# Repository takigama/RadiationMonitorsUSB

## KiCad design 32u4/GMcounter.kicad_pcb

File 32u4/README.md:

Geiger Counter
==============

Based on MightyOhms GM Device, this is an SMD version of that device
with a 32u4 atmel chip onboard.

Tag firtprint has now been sent to the printer and looks like this:

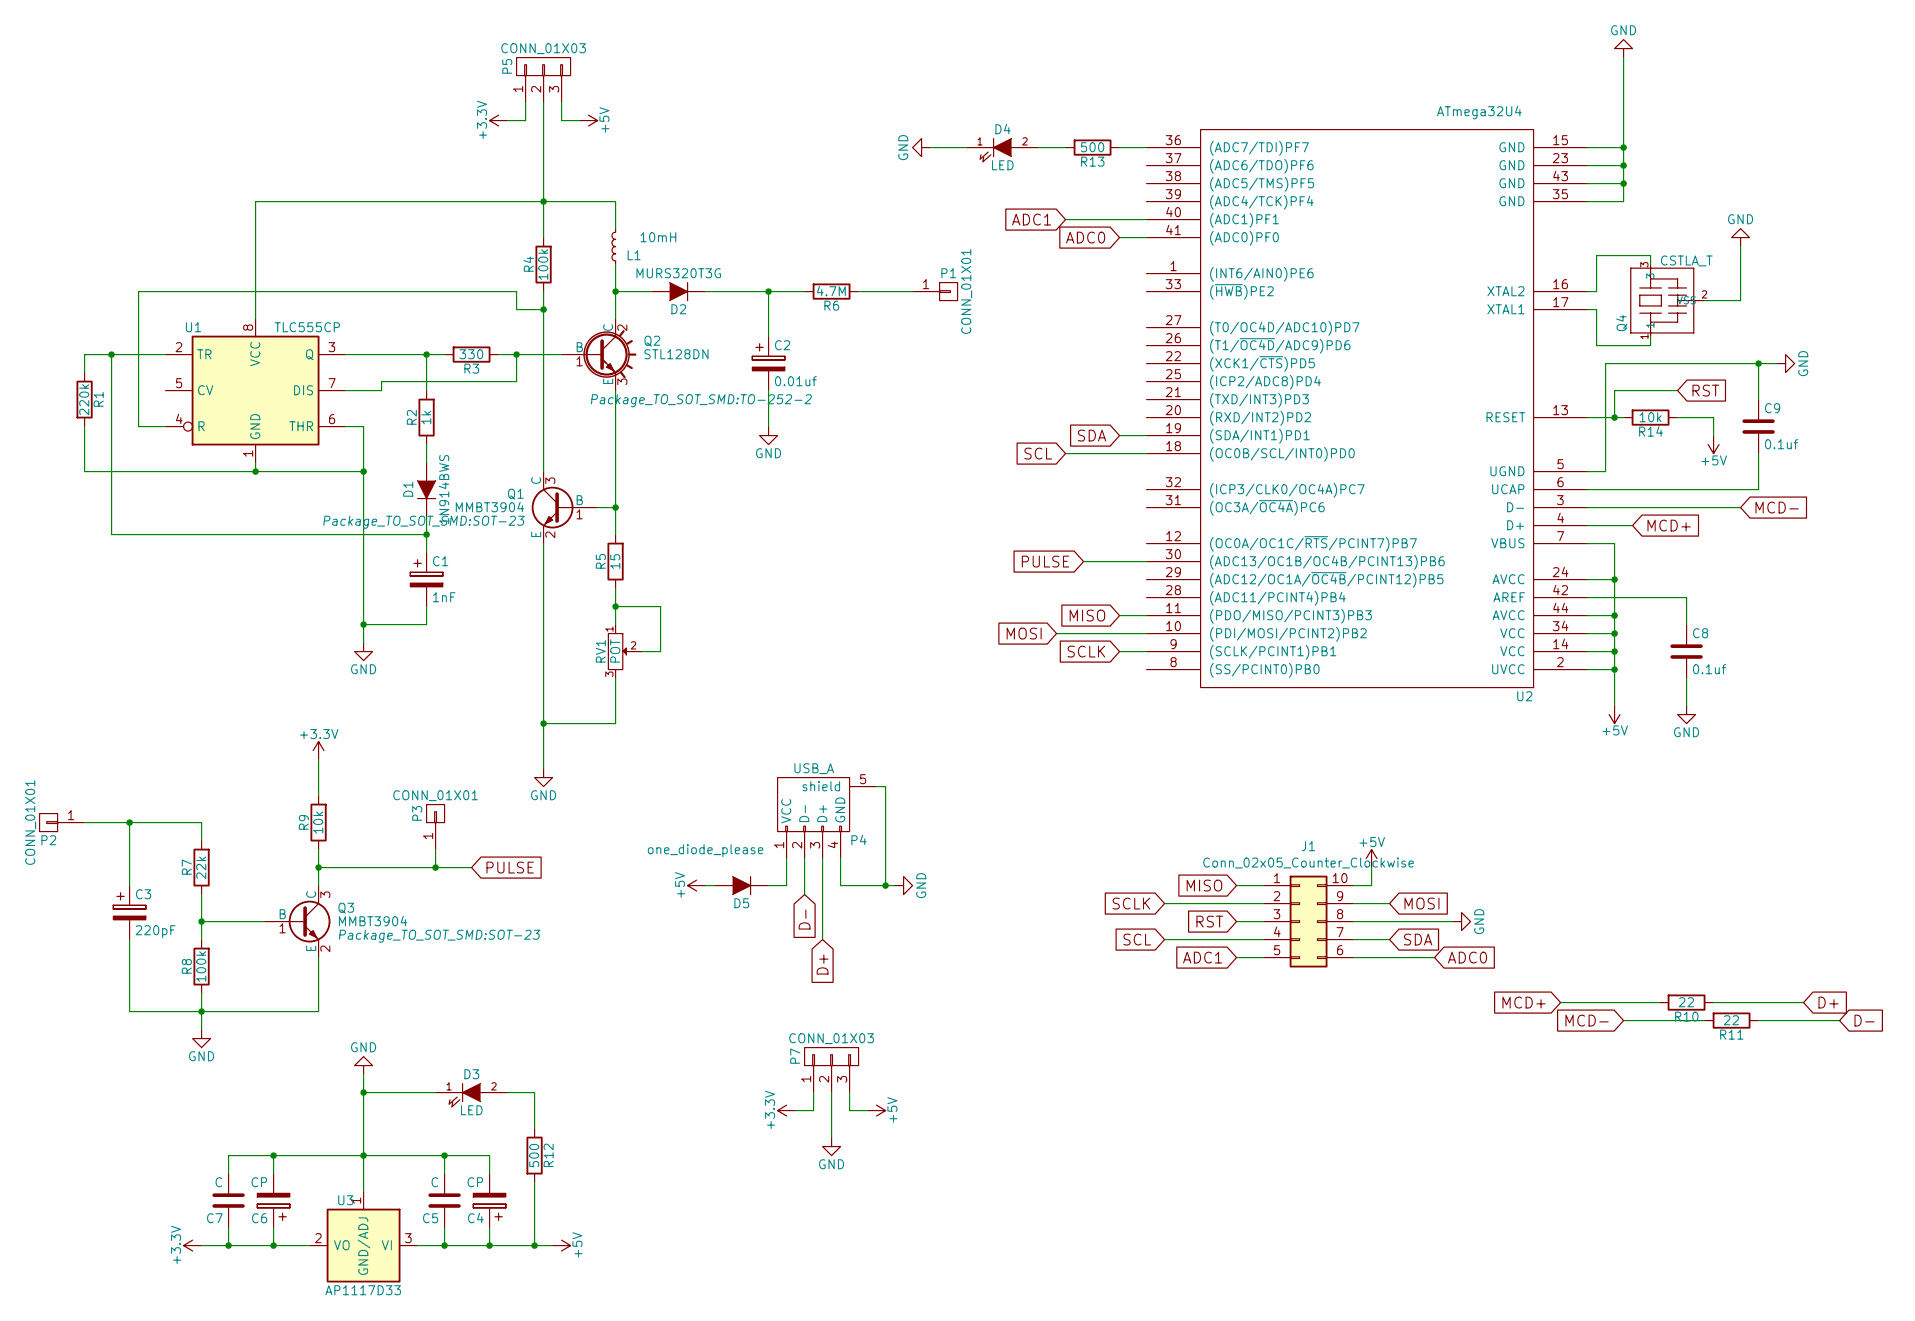
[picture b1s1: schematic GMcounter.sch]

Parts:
C1: 1nF; CP_EIA-3216-12_Kemet-S
C2: 0.01uf; CP_EIA-3216-12_Kemet-S
C3: 220pF; CP_EIA-3216-12_Kemet-S
C4, C6: CP; CP_EIA-3216-12_Kemet-S
C5, C7: C; C_1206_3216Metric
C8, C9: 0.1uf; C_1206_3216Metric
D1: 1N914BWS; D_SOD-323
D2: MURS320T3G; D_SMC
D3, D4: LED; D_0805_2012Metric
D5: one_diode_please; D_SMA
J1: Conn_02x05_Counter_Clockwise; PinHeader_2x05_P2.54mm_Vertical
L1: 10mH; SRR1208
P1, P2, P3: CONN_01X01; PinHeader_1x01_P2.54mm_Vertical
P4: USB_A; USB_Micro-B-OshPark
P5, P7: CONN_01X03; PinHeader_1x03_P2.54mm_Vertical
Q1, Q3: MMBT3904; SOT-23
Q2: STL128DN; TO-252-2
Q4: CSTLA_T; Murata-16mhz-Resonator
R1: 220k; R_1206_3216Metric
R2: 1k; R_1206_3216Metric
R3: 330; R_1206_3216Metric
R4, R8: 100k; R_1206_3216Metric
R5: 15; R_1206_3216Metric
R6: 4.7M; R_1206_3216Metric
R7: 22k; R_1206_3216Metric
R9, R14: 10k; R_1206_3216Metric
R10, R11: 22; R_1206_3216Metric
R12, R13: 500; R_1206_3216Metric
RV1: POT; Potentiometer_Bourns_3296W_Vertical
U1: TLC555CP; SOIC-8_3.9x4.9mm_P1.27mm
U2: ATmega32U4; TQFP-44_10x10mm_P0.8mm
U3: AP1117D33; SOT-223

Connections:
+3V3: C6.1, C7.1, P5.1, P7.1, R9.2, U3.2 (VO)
+5V: C4.1, C5.1, D5.2 (A), J1.10, P5.3, P7.3, R12.2, R14.1, U2.2 (UVCC), U2.7 (VBUS), U2.14 (VCC), U2.24 (AVCC), U2.34 (VCC), U2.44 (AVCC), U3.3 (VI)
ADC0: J1.6, U2.41 ((ADC0)PF0)
ADC1: J1.5, U2.40 ((ADC1)PF1)
D+: P4.3 (D+), R10.1
D-: P4.2 (D-), R11.1
GND: C1.2, C2.2, C3.2, C4.2, C5.2, C6.2, C7.2, C8.2, C9.1, D3.1 (K), D4.1 (K), J1.8, P4.4 (GND), P4.5 (shield), P7.2, Q1.2 (E), Q3.2 (E), Q4.2 (VSS), R1.2, R8.1, RV1.3, U1.1 (GND), U1.6 (THR), U2.5 (UGND), U2.15 (GND), U2.23 (GND), U2.35 (GND), U2.43 (GND), U3.1 (GND/ADJ)
MCD+: R10.2, U2.4 (D+)
MCD-: R11.2, U2.3 (D-)
MISO: J1.1, U2.11 ((PDO/MISO/PCINT3)PB3)
MOSI: J1.9, U2.10 ((PDI/MOSI/PCINT2)PB2)
unnamed: C1.1, D1.1 (K), R1.1, U1.2 (TR)
unnamed: C2.1, D2.1 (K), R6.2
unnamed: C3.1, P2.1, R7.2
unnamed: C8.1, U2.42 (AREF)
unnamed: C9.2, U2.6 (UCAP)
unnamed: D1.2 (A), R2.1
unnamed: D2.2 (A), L1.1, Q2.2 (C)
unnamed: D3.2 (A), R12.1
unnamed: D4.2 (A), R13.2
unnamed: D5.1 (K), P4.1 (VCC)
unnamed: L1.2, P5.2, R4.2, U1.8 (VCC)
unnamed: P1.1, R6.1
unnamed: Q1.1 (B), Q2.3 (E), R5.2
unnamed: Q1.3 (C), R4.1, U1.4 (R)
unnamed: Q2.1 (B), R3.1, U1.7 (DIS)
unnamed: Q3.1 (B), R7.1, R8.2
unnamed: Q4.1, U2.17 (XTAL1)
unnamed: Q4.3, U2.16 (XTAL2)
unnamed: R2.2, R3.2, U1.3 (Q)
unnamed: R5.1, RV1.1, RV1.2
unnamed: R13.1, U2.36 ((ADC7/TDI)PF7)
PULSE: P3.1, Q3.3 (C), R9.1, U2.30 ((ADC13/OC1B/OC4B/PCINT13)PB6)
RST: J1.3, R14.2, U2.13 (RESET)
SCL: J1.4, U2.18 ((OC0B/SCL/INT0)PD0)
SCLK: J1.2, U2.9 ((SCLK/PCINT1)PB1)
SDA: J1.7, U2.19 ((SDA/INT1)PD1)

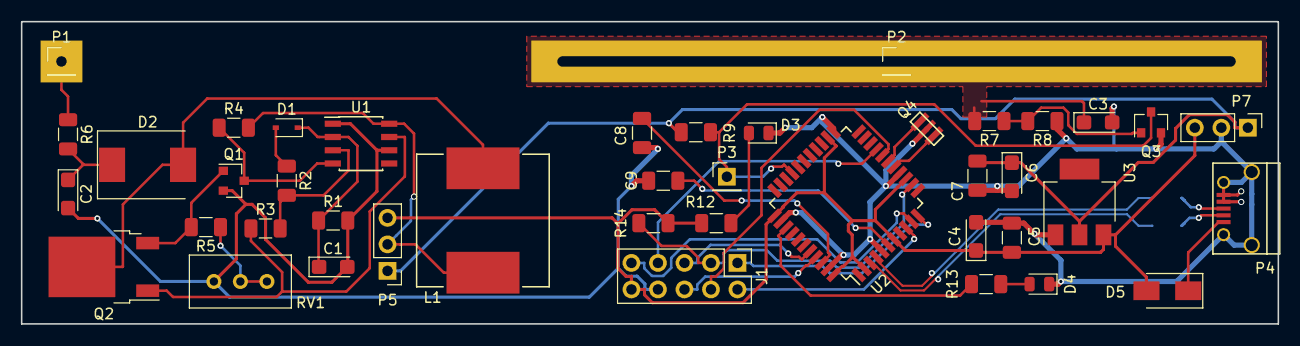
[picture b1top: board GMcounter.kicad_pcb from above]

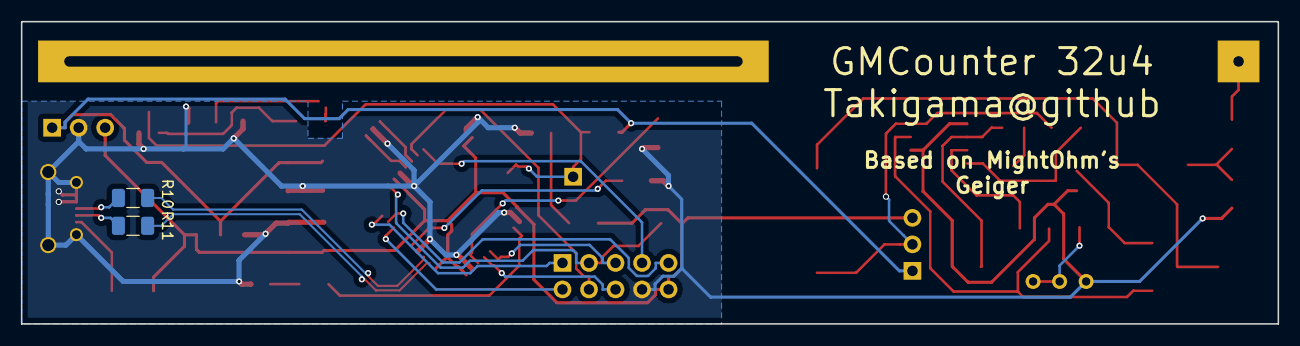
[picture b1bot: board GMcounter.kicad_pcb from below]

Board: 2 copper layers, 120.4 x 29.0 mm, 44 parts (2 on the bottom side), 37 nets.

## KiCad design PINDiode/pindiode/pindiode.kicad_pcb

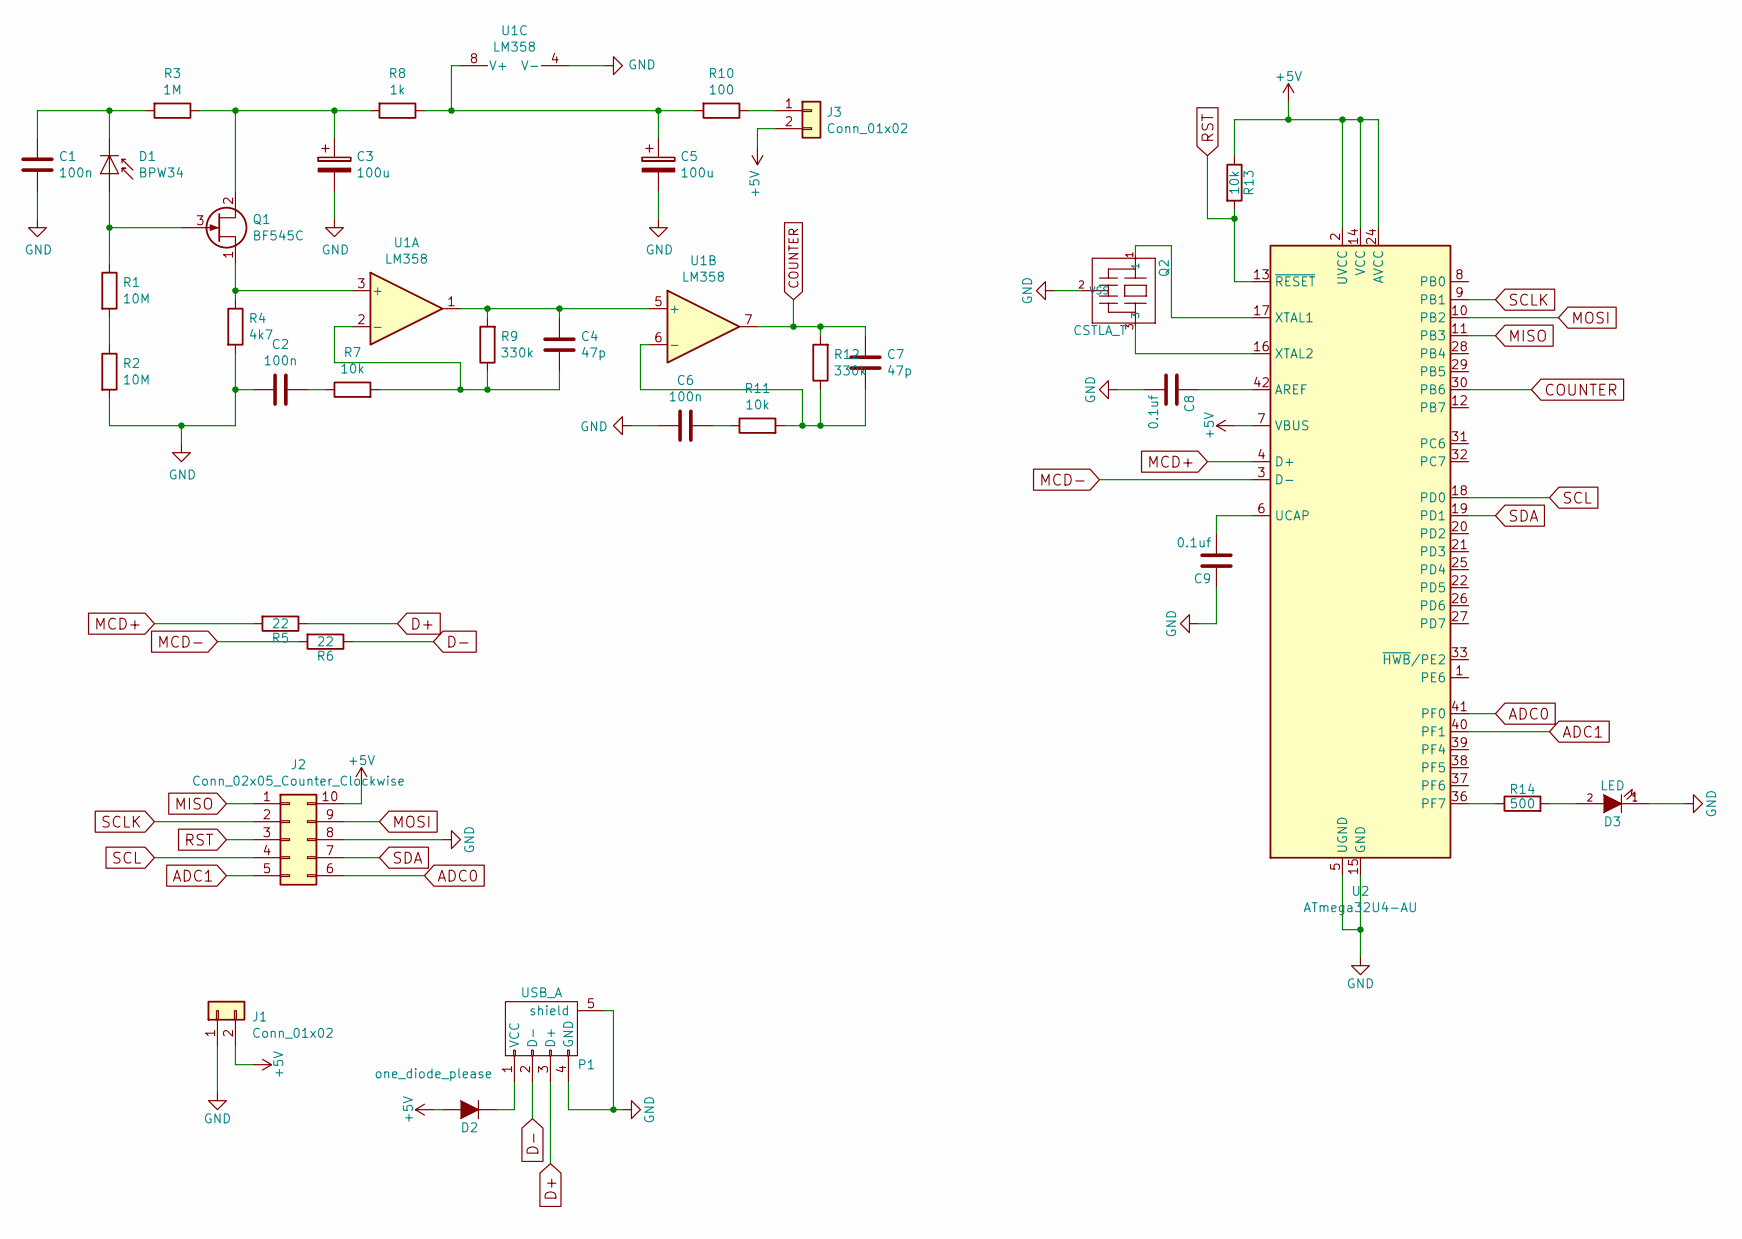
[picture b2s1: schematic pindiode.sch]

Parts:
C1, C2, C6: 100n; C_1206_3216Metric
C3, C5: 100u; CP_EIA-3216-10_Kemet-I
C4, C7: 47p; C_1206_3216Metric
C8, C9: 0.1uf; C_1206_3216Metric
D1: BPW34; Osram_DIL2_4.3x4.65mm_P5.08mm
D2: one_diode_please; D_SMA
D3: LED; D_0805_2012Metric
J1, J3: Conn_01x02; PinHeader_1x02_P2.54mm_Vertical
J2: Conn_02x05_Counter_Clockwise; PinHeader_2x05_P2.54mm_Vertical
P1: USB_A; USB_Micro-B-OshPark
Q1: BF545C; SOT-23
Q2: CSTLA_T; Murata-16mhz-Resonator
R1, R2: 10M; R_1206_3216Metric
R3: 1M; R_1206_3216Metric
R4: 4k7; R_1206_3216Metric
R5, R6: 22; R_1206_3216Metric
R7, R11, R13: 10k; R_1206_3216Metric
R8: 1k; R_1206_3216Metric
R9, R12: 330k; R_1206_3216Metric
R10: 100; R_1206_3216Metric
R14: 500; R_1206_3216Metric
U1: LM358; SOIC-8_3.9x4.9mm_P1.27mm
U2: ATmega32U4-AU; TQFP-44_10x10mm_P0.8mm

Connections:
+5V: D2.2 (A), J1.2, J2.10, J3.2, R13.1, U2.2 (UVCC), U2.7 (VBUS), U2.14 (VCC), U2.24 (AVCC), U2.34 (VCC), U2.44 (AVCC)
ADC0: J2.6, U2.41 (PF0)
ADC1: J2.5, U2.40 (PF1)
COUNTER: C7.1, R12.2, U1.7, U2.30 (PB6)
D+: P1.3 (D+), R5.1
D-: P1.2 (D-), R6.1
GND: C1.2, C2.1, C3.2, C5.2, C6.1, C8.2, C9.1, D3.1 (K), J1.1, J2.8, P1.4 (GND), P1.5 (shield), Q2.2 (VSS), R2.2, R4.2, U1.4 (V-), U2.5 (UGND), U2.15 (GND), U2.23 (GND), U2.35 (GND), U2.43 (GND)
MCD+: R5.2, U2.4 (D+)
MCD-: R6.2, U2.3 (D-)
MISO: J2.1, U2.11 (PB3)
MOSI: J2.9, U2.10 (PB2)
unnamed: C1.1, D1.1 (K), R3.2
unnamed: C2.2, R7.1
unnamed: C3.1, Q1.2 (D), R3.1, R8.2
unnamed: C4.1, R9.2, U1.1, U1.5 (+)
unnamed: C4.2, R7.2, R9.1, U1.2 (-)
unnamed: C5.1, R8.1, R10.2, U1.8 (V+)
unnamed: C6.2, R11.1
unnamed: C7.2, R11.2, R12.1, U1.6 (-)
unnamed: C8.1, U2.42 (AREF)
unnamed: C9.2, U2.6 (UCAP)
unnamed: D1.2 (A), Q1.3 (G), R1.1
unnamed: D2.1 (K), P1.1 (VCC)
unnamed: D3.2 (A), R14.2
unnamed: J3.1, R10.1
unnamed: Q1.1 (S), R4.1, U1.3 (+)
unnamed: Q2.1, U2.17 (XTAL1)
unnamed: Q2.3, U2.16 (XTAL2)
unnamed: R1.2, R2.1
unnamed: R14.1, U2.36 (PF7)
RST: J2.3, R13.2, U2.13 (~RESET)
SCL: J2.4, U2.18 (PD0)
SCLK: J2.2, U2.9 (PB1)
SDA: J2.7, U2.19 (PD1)

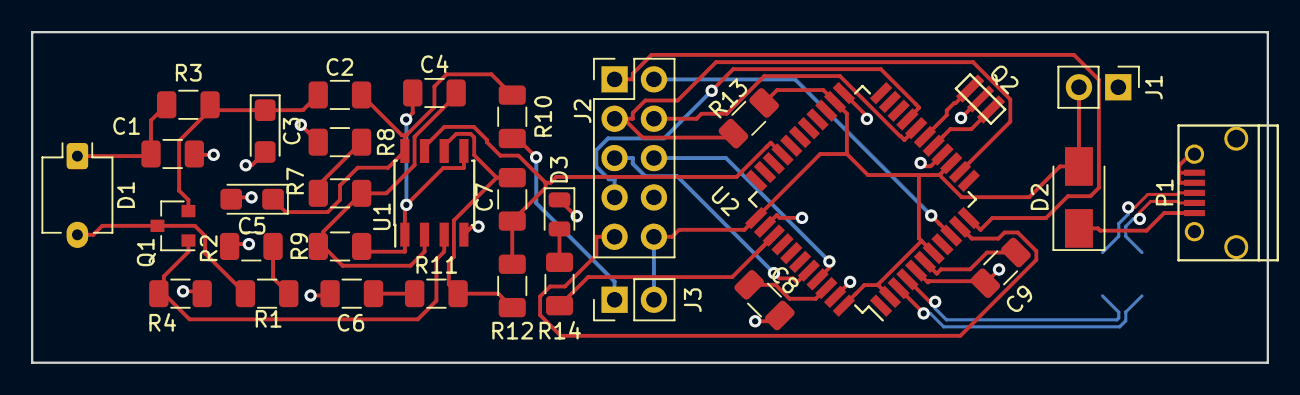
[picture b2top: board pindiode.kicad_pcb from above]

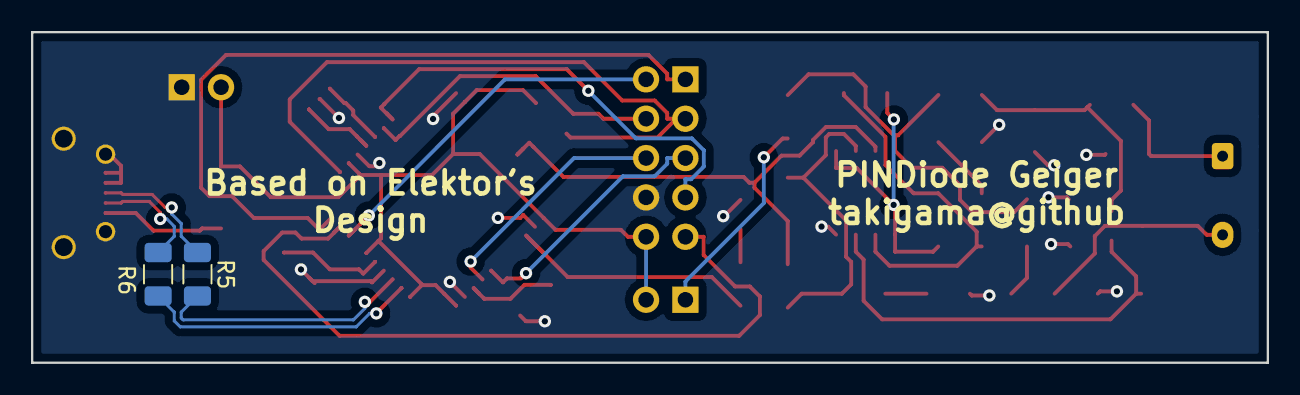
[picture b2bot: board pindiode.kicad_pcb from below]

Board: 2 copper layers, 79.8 x 21.3 mm, 34 parts (2 on the bottom side), 34 nets.

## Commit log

2018-11-07 initial
2018-11-07 pdate
2018-11-07 updated with proper resonator footprint
2018-11-09 changed foot print for inductor, changed design rules
2018-11-09 some manual routing for diff pairs and crystal
2018-11-13 pre-5.0 test
2018-11-13 updated to kicad 5
2018-11-13 updated image with smaller footprint
2018-11-17 first version to printer
2018-11-19 initial pindiode layout
2018-11-22 per-auto router
2018-12-22 added pic
2018-12-22 resize
